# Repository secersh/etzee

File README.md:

# etzee

etzee is an open modular input-device ecosystem. It combines keyboards, utility modules, magnetic pogo-pin connectors, local displays, haptics, and firmware that can discover and communicate across connected modules.

The project is early and hardware-heavy. The current active board is B11; M0 and M9 are planned modules.

## Devices

| Device | Type | Status | Notes |
|--------|------|--------|-------|
| B11 | Primary keyboard board | Active | Split or monoblock keyboard, 5/6 columns per half, switch-family PCB variants |
| M0 | Module | Planned | USB-C module with haptic dial and round touch display |
| M9 | Module | Planned | USB-C 3x3 mechanical keypad with display |

## B11

B11 is the first primary etzee keyboard. Current design goals:

- split or monoblock use
- Bluetooth-first firmware target
- hot-swappable switch carriers
- integrated dot-matrix display on switch plates
- south-facing per-key LEDs
- magnetic pogo-pin module connectors
- 5-column and 6-column half variants
- MX, Choc v2, and KS-33 switch-family variants
- generated KiCad PCB files from tracked MCAD-derived outlines

Current B11 docs:

- [switch compatibility](docs/b11/switch-compatibility.md)
- [switch profiles](docs/b11/switch-profiles.md)
- [keycap compatibility](docs/b11/keycap-compatibility.md)

## Repository Layout

```text
.github/workflows/          GitHub Actions workflows
docs/b11/                   B11 hardware compatibility and profile docs
docs/firmware/              firmware and protocol docs
firmware/                   firmware workspaces
hardware/b11/ecad/          B11 KiCad projects and generated boards
hardware/b11/mcad/          B11 MCAD export config and PCB outlines
hardware/b11/tools/         B11 PCB generation/update tools
hardware/tools/             shared hardware tooling
lib/                        shared KiCad footprints, 3D models, datasheets
```

## Generated PCB Workflow

B11 generated boards are updated through one batch script:

```sh
/Applications/KiCad/KiCad.app/Contents/Frameworks/Python.framework/Versions/Current/bin/python3 hardware/b11/tools/update-pcbs.py --manufacturer jlcpcb --dry-run
```

Remove `--dry-run` to update generated PCB files locally. The updater can generate PCB outlines, place switch sockets, place switch LEDs, place display LEDs, apply manufacturer stackups, and generate manufacturer design rules.

Current generated B11 PCB variants:

| Family | Columns | Boards |
|--------|---------|--------|
| MX | 5, 6 | `LSP`, `RSP`, `LSC`, `RSC` |
| CHOC-V2 | 5, 6 | `LSP`, `RSP`, `LSC`, `RSC` |
| KS-33 | 5, 6 | `LSP`, `RSP`, `LSC`, `RSC` |

Board names use:

```text
ETZ-B11-{board_code}-{columns}-{switch_family}.kicad_pcb
```

Example:

```text
ETZ-B11-LSP-5-KS-33.kicad_pcb
```

## MCAD Exports

B11 MCAD export inputs are defined in [hardware/b11/mcad/parts.yaml](hardware/b11/mcad/parts.yaml). The GitHub workflow exports common parts once and matrix parts once per board variant:

- `5-MX`, `6-MX`
- `5-CHOC-V2`, `6-CHOC-V2`
- `5-KS-33`, `6-KS-33`

PCB outline DXFs live under:

```text
hardware/b11/mcad/pcb-outlines/{MX,CHOC-V2,KS-33}/
```

## Firmware

Firmware is based around ZMK-compatible targets. The htoyto protocol is the project-specific communication concept for inter-module discovery and messaging.

- [htoyto protocol overview](docs/firmware/htoyto.md)

## Contributing

See [CONTRIBUTING.md](CONTRIBUTING.md). The short version: keep generated files reproducible, keep hardware changes scoped, and run the relevant dry-runs before opening a pull request.

For discussion and implementation feedback, join the etzee Discord:

https://discord.gg/y3pcSCghcg

## License

This repository uses different open licenses for different material types. See [LICENSE.md](LICENSE.md) for the full licensing map.

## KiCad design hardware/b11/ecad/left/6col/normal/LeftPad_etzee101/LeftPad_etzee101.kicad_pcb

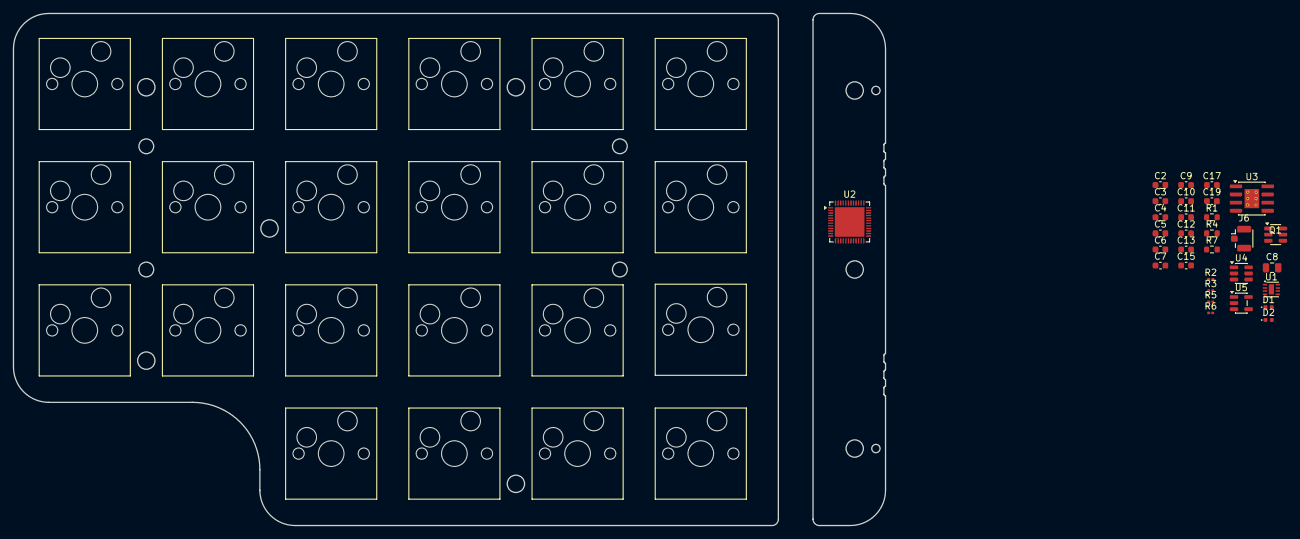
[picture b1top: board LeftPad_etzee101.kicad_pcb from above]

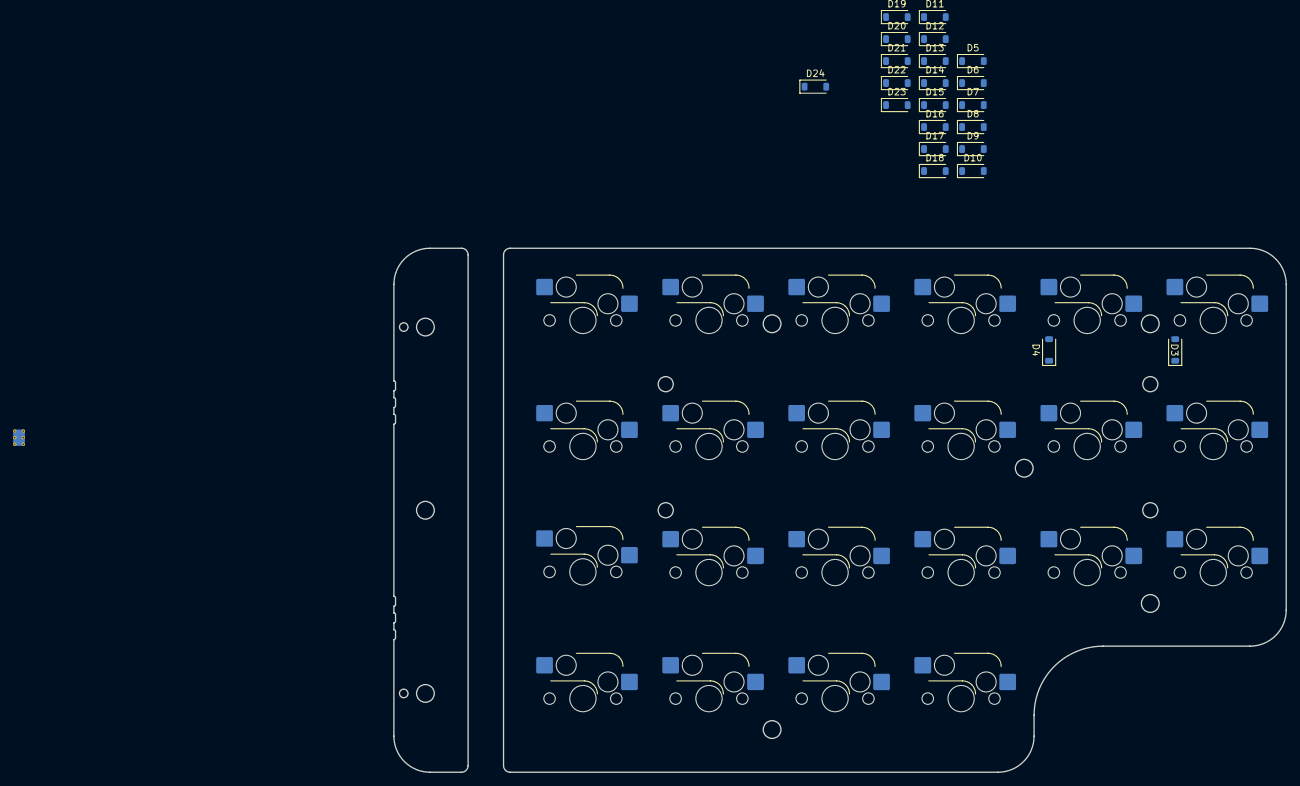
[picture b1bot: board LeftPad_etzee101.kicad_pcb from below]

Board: 4 copper layers, 135.9 x 79.8 mm, 75 parts (22 on the bottom side), 58 nets, no tracks yet.

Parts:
C2: 1uF; C_0603_1608Metric
C3, C4: 100pF; C_0603_1608Metric
C5: 100nF; C_0603_1608Metric
C6, C13, C17, C19: 12pF; C_0603_1608Metric
C7, C12: 100n; C_0603_1608Metric
C8: 10u; C_0805_2012Metric
C9: 1u; C_0603_1608Metric
C10: 10n; C_0603_1608Metric
C11: 10u; C_0603_1608Metric
C15: 1pF; C_0603_1608Metric
D1: RED; D_0402_1005Metric
D2: GRN; D_0402_1005Metric
D3, D4, D5, D6, D7, D8, D9, D10, D11, D12, D13, D14, D15, D16, D17, D18, D19, D20, D21, D22, D23, D24: 1n4148; D_SOD-123
J6: FL; U.FL_Hirose_U.FL-R-SMT-1_Vertical
Q1: FS8205A; FS8205A_SOT23-6
R1: 100; R_0603_1608Metric
R2, R3, R5, R6: 1K2; R_0201_0603Metric
R4, R7: 10K; R_0603_1608Metric
SW1, SW2, SW3, SW4, SW5, SW6, SW7, SW8, SW9, SW10, SW11, SW12, SW13, SW14, SW15, SW16, SW17, SW18, SW19, SW20, SW21, SW22: MX_Switch_Hot_Swappable
U1: MAX17048G; DFN-8-1EP_2x2mm_P0.5mm_EP0.8x1.6mm
U2: nRF52832-QFxx; QFN-48-1EP_6x6mm_P0.4mm_EP4.6x4.6mm
U3: TP4056; SOIC-8-1EP_3.9x4.9mm_P1.27mm_EP2.29x3mm_ThermalVias
U4: DW01; SOT-23-6
U5: XC6220B331MR; SOT-23-5

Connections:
+5V: D1.2 (A), D2.2 (A), U3.4 (VCC), U3.8 (CE)
+VBAT: C8.1, C9.1, C10.1, R1.2, R7.2, U1.2 (CELL), U1.3 (VDD), U3.5 (BAT), U5.1 (VIN)
/ALRT_BAT: R4.2, U1.5 (ALT)
/keyboard_pad_left/COL1: SW1.1, SW7.1, SW13.1
/keyboard_pad_left/COL2: SW2.1, SW8.1, SW14.1
/keyboard_pad_left/COL3: SW3.1, SW9.1, SW15.1, SW19.1
/keyboard_pad_left/COL4: SW4.1, SW10.1, SW16.1, SW20.1
/keyboard_pad_left/COL5: SW5.1, SW11.1, SW17.1, SW21.1
/keyboard_pad_left/COL6: SW6.1, SW12.1, SW18.1, SW22.1
/keyboard_pad_left/ROW1: D3.1 (K), D4.1 (K), D6.1 (K), D7.1 (K), D8.1 (K), D21.1 (K)
/keyboard_pad_left/ROW2: D5.1 (K), D9.1 (K), D10.1 (K), D11.1 (K), D12.1 (K), D22.1 (K)
/keyboard_pad_left/ROW3: D13.1 (K), D14.1 (K), D15.1 (K), D16.1 (K), D17.1 (K), D23.1 (K)
/keyboard_pad_left/ROW4: D18.1 (K), D19.1 (K), D20.1 (K), D24.1 (K)
GND: C2.2, C3.2, C4.2, C5.2, C6.2, C8.2, C9.2, C10.2, C11.2, C12.2, C13.2, C15.2, C17.2, C19.2, J6.2 (Ext), R2.2, U1.1 (CTG), U1.4 (GND), U1.6 (QST), U1.9 (EP), U2.31 (VSS), U2.45 (VSS), U2.49 (VSS), U3.1 (TEMP), U3.3 (GND), U3.9 (EP), U5.2 (GND)
unnamed: D1.1 (K), R3.1
unnamed: D2.1 (K), R5.1
unnamed: D3.2 (A), SW1.2
unnamed: D4.2 (A), SW2.2
unnamed: D5.2 (A), SW7.2
unnamed: D6.2 (A), SW3.2
unnamed: D7.2 (A), SW4.2
unnamed: D8.2 (A), SW5.2
unnamed: D9.2 (A), SW8.2
unnamed: D10.2 (A), SW9.2
unnamed: D11.2 (A), SW10.2
unnamed: D12.2 (A), SW11.2
unnamed: D13.2 (A), SW13.2
unnamed: D14.2 (A), SW14.2
unnamed: D15.2 (A), SW15.2
unnamed: D16.2 (A), SW16.2
unnamed: D17.2 (A), SW17.2
unnamed: D18.2 (A), SW19.2
unnamed: D19.2 (A), SW20.2
unnamed: D20.2 (A), SW21.2
unnamed: D21.2 (A), SW6.2
unnamed: D22.2 (A), SW12.2
unnamed: D23.2 (A), SW18.2
unnamed: D24.2 (A), SW22.2
unnamed: C7.2, Q1.D1/D2, U4.4 (TD)
unnamed: Q1.S1, R6.2
unnamed: C15.1, U2.30 (ANT)
unnamed: C5.1, U2.1 (DEC1)
unnamed: C4.1, U2.32 (DEC2)
unnamed: C3.1, U2.33 (DEC3)
unnamed: C2.1, U2.46 (DEC4)
unnamed: C6.1, U2.2 (P0.00/XL1)
unnamed: C13.1, U2.3 (P0.01/XL2)
unnamed: C17.1, U2.34 (XC1)
unnamed: C19.1, U2.35 (XC2)
unnamed: R3.2, U3.7 (CHRG)
unnamed: R2.1, U3.2 (PROG)
unnamed: R5.2, U3.6 (STDBY)
unnamed: C7.1, R1.1, U4.2 (CS)
unnamed: Q1.G2, U4.3 (OC)
unnamed: Q1.G1, U4.1 (OD)
unnamed: R6.1, U4.5 (VCC)
unnamed: R7.1, U5.3 (CE)
VDD: C11.1, C12.1, R4.1, U2.13 (VDD), U2.36 (VDD), U2.48 (VDD), U5.5 (VOUT)

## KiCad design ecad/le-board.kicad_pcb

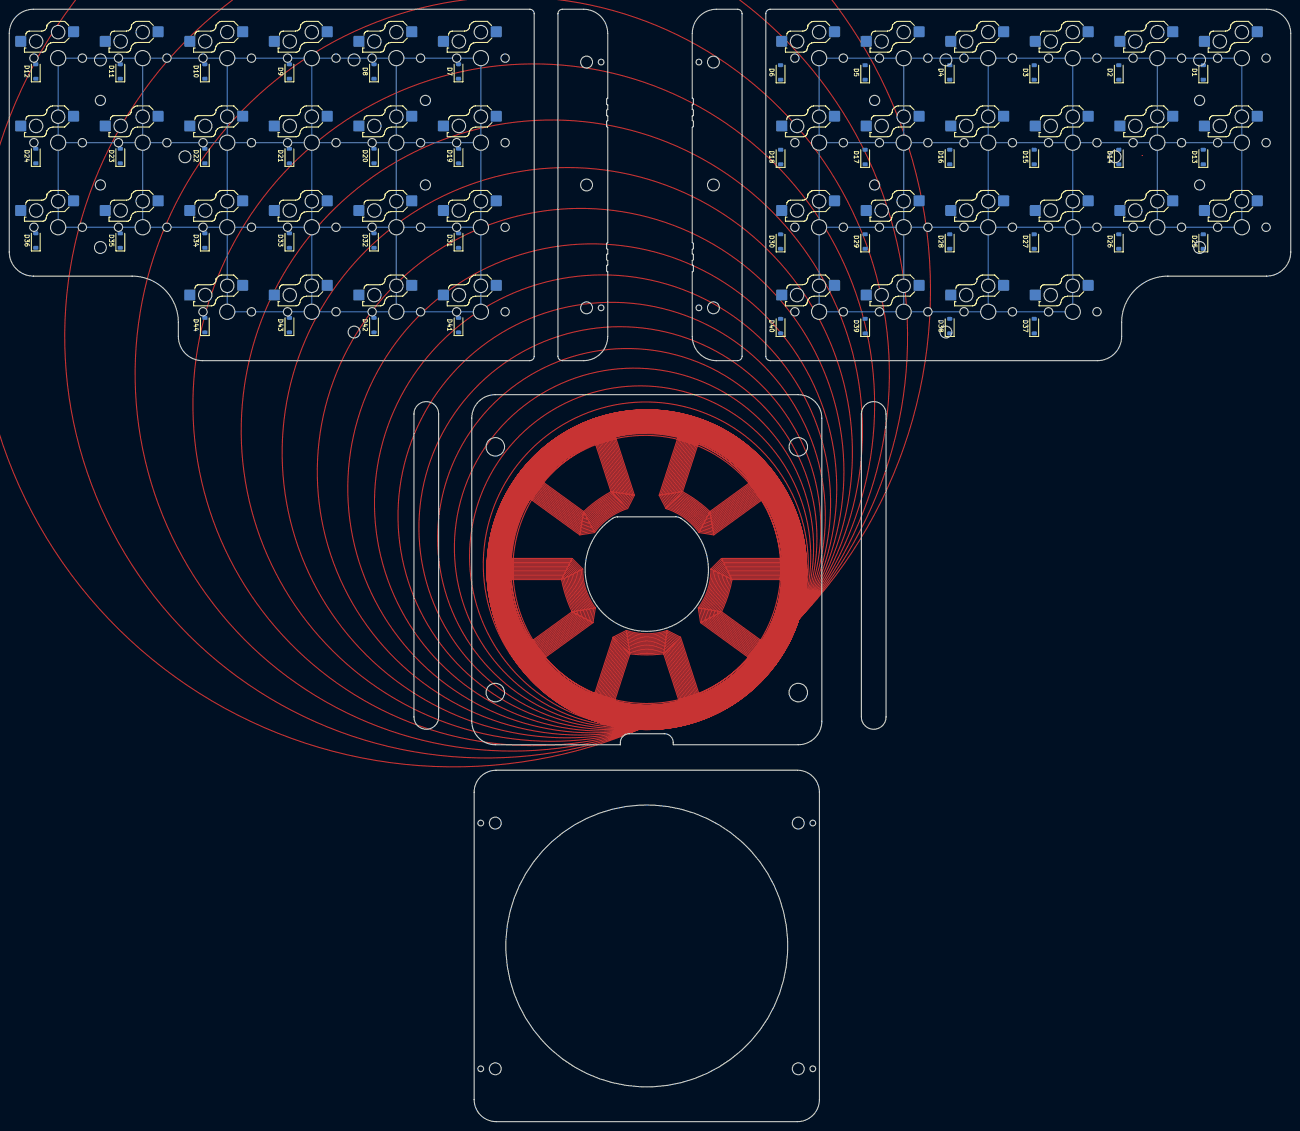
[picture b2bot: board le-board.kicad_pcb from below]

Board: 4 copper layers, 291.0 x 252.6 mm, 88 parts (44 on the bottom side), 44 nets.

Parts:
D1, D2, D3, D4, D5, D6, D7, D8, D9, D10, D11, D12, D13, D14, D15, D16, D17, D18, D19, D20, D21, D22, D23, D24, D25, D26, D27, D28, D29, D30, D31, D32, D33, D34, D35, D36, D37, D38, D39, D40, D41, D42, D43, D44: 1n4148; D_SOD-123
MX1, MX2, MX3, MX4, MX5, MX6, MX7, MX8, MX9, MX10, MX11, MX12, MX13, MX14, MX15, MX16, MX17, MX18, MX19, MX20, MX21, MX22, MX23, MX24, MX25, MX26, MX27, MX28, MX29, MX30, MX31, MX32, MX33, MX34, MX35, MX36, MX37, MX38, MX39, MX40, MX41, MX42, MX43, MX44: SW; SW_Hotswap_Kailh_Choc_V1

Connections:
unnamed: D1.2 (A), MX1.2
unnamed: D2.2 (A), MX2.2
unnamed: D3.2 (A), MX3.2
unnamed: D4.2 (A), MX4.2
unnamed: D5.2 (A), MX5.2
unnamed: D6.2 (A), MX6.2
unnamed: D7.2 (A), MX7.2
unnamed: D8.2 (A), MX8.2
unnamed: D9.2 (A), MX9.2
unnamed: D10.2 (A), MX10.2
unnamed: D11.2 (A), MX11.2
unnamed: D12.2 (A), MX12.2
unnamed: D13.2 (A), MX13.2
unnamed: D14.2 (A), MX14.2
unnamed: D15.2 (A), MX15.2
unnamed: D16.2 (A), MX16.2
unnamed: D17.2 (A), MX17.2
unnamed: D18.2 (A), MX18.2
unnamed: D19.2 (A), MX19.2
unnamed: D20.2 (A), MX20.2
unnamed: D21.2 (A), MX21.2
unnamed: D22.2 (A), MX22.2
unnamed: D23.2 (A), MX23.2
unnamed: D24.2 (A), MX24.2
unnamed: D25.2 (A), MX25.2
unnamed: D26.2 (A), MX26.2
unnamed: D27.2 (A), MX27.2
unnamed: D28.2 (A), MX28.2
unnamed: D29.2 (A), MX29.2
unnamed: D30.2 (A), MX30.2
unnamed: D31.2 (A), MX31.2
unnamed: D32.2 (A), MX32.2
unnamed: D33.2 (A), MX33.2
unnamed: D34.2 (A), MX34.2
unnamed: D35.2 (A), MX35.2
unnamed: D36.2 (A), MX36.2
unnamed: D37.2 (A), MX37.2
unnamed: D38.2 (A), MX38.2
unnamed: D39.2 (A), MX39.2
unnamed: D40.2 (A), MX40.2
unnamed: D41.2 (A), MX41.2
unnamed: D42.2 (A), MX42.2
unnamed: D43.2 (A), MX43.2
unnamed: D44.2 (A), MX44.2

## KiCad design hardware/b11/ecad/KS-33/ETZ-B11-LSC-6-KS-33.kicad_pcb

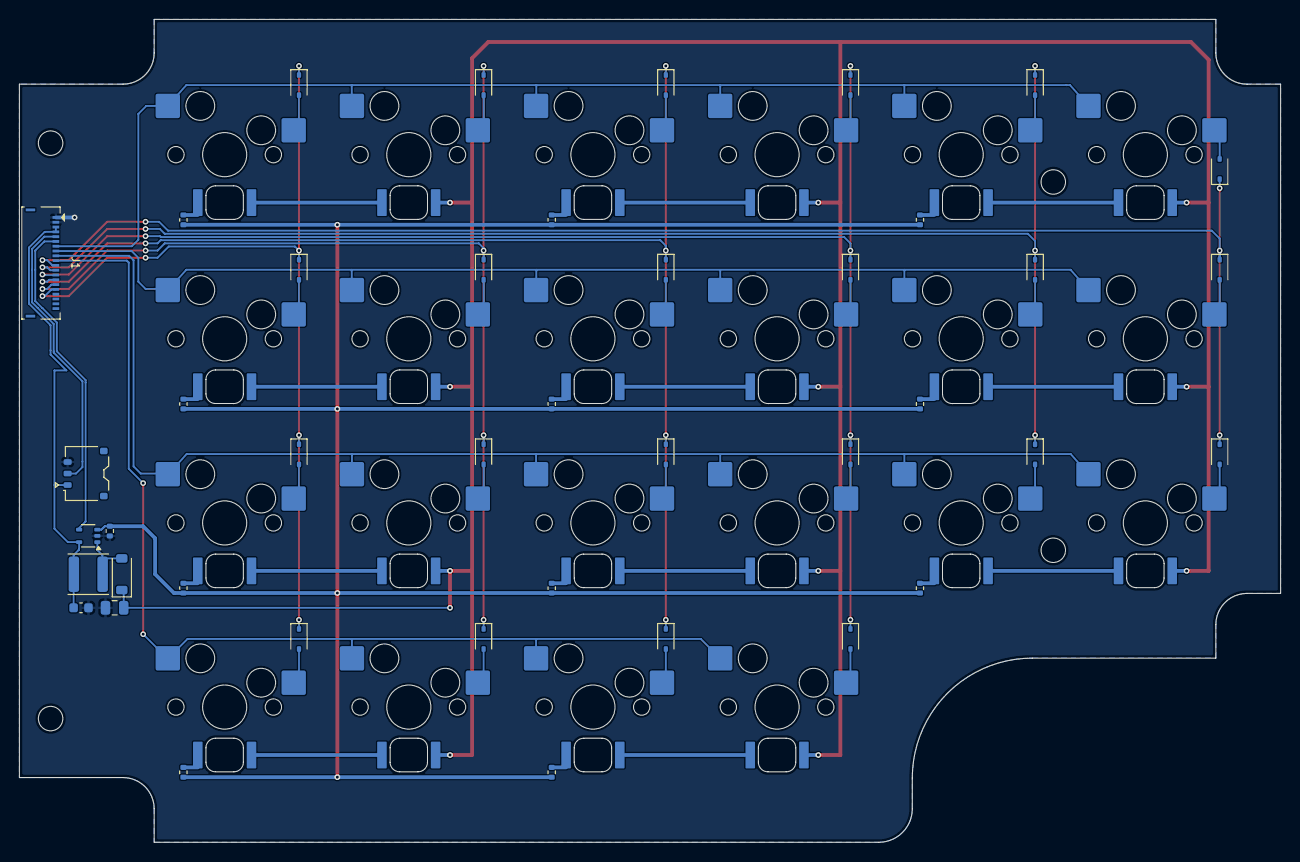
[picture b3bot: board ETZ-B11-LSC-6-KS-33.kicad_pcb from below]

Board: 2 copper layers, 131.5 x 85.8 mm, 85 parts (41 on the bottom side), 61 nets.

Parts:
C1: 4.7uF 10V; C_0603_1608Metric
C2: 1uF 50V; C_0805_2012Metric
D1, D2, D3, D4, D5, D6, D7, D8, D9, D10, D11, D12, D13, D14, D15, D16, D17, D18, D19, D20, D21, D22: 1N4148WS
D23: B5819W; D_SOD-123
J1: 503480-2000
J2: BM03B-ACHSS-GAN-ETF
L1: SWPA4018S100MT; L_Sunlord_SWPA4018S
LED1, LED2, LED3, LED4, LED5, LED6, LED7, LED8, LED9, LED10, LED11, LED12, LED13, LED14, LED15, LED16, LED17, LED18, LED19, LED20, LED21, LED22: 6028_LED
R1: 3.74R 1%; R_0402_1005Metric
R2, R3, R4, R5, R6, R7, R8, R9, R10, R11, R12: 220R 1%; R_0402_1005Metric
SW1, SW2, SW3, SW4, SW5, SW6, SW7, SW8, SW9, SW10, SW11, SW12, SW13, SW14, SW15, SW16, SW17, SW18, SW19, SW20, SW21, SW22: KS-2P02B01-01-a
U1: TPS61169; SOT-353_SC-70-5

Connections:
/BAT_NTC: J1.5, J2.2
/BL_PWM: J1.6, U1.4
/COL0: D1.1, D7.1, D13.1, J1.11
/COL1: D2.1, D8.1, D14.1, J1.12
/COL2: D3.1, D9.1, D15.1, D19.1, J1.13
/COL3: D4.1, D10.1, D16.1, D20.1, J1.14
/COL4: D5.1, D11.1, D17.1, D21.1, J1.15
/COL5: D6.1, D12.1, D18.1, D22.1, J1.16
/ROW0: J1.7, SW1.1, SW2.1, SW3.1, SW4.1, SW5.1, SW6.1
/ROW1: J1.8, SW7.1, SW8.1, SW9.1, SW10.1, SW11.1, SW12.1
/ROW2: J1.9, SW13.1, SW14.1, SW15.1, SW16.1, SW17.1, SW18.1
/ROW3: J1.10, SW19.1, SW20.1, SW21.1, SW22.1
/VBAT: C1.1, J1.3, J1.4, J2.1, L1.1, U1.5
GND: C1.2, C2.2, J1.1, J1.2, J2.3, R1.2, U1.2
unnamed: D23.2, L1.2, U1.1
unnamed: C2.1, D23.1, LED1.2, LED3.2, LED5.2, LED7.2, LED9.2, LED11.2, LED13.2, LED15.2, LED17.2, LED19.2, LED21.2
unnamed: LED1.1, LED2.2
unnamed: LED2.1, R2.1
unnamed: LED3.1, LED4.2
unnamed: LED4.1, R3.1
unnamed: LED5.1, LED6.2
unnamed: LED6.1, R4.1
unnamed: LED7.1, LED8.2
unnamed: LED8.1, R5.1
unnamed: LED9.1, LED10.2
unnamed: LED10.1, R6.1
unnamed: LED11.1, LED12.2
unnamed: LED12.1, R7.1
unnamed: LED13.1, LED14.2
unnamed: LED14.1, R8.1
unnamed: LED15.1, LED16.2
unnamed: LED16.1, R9.1
unnamed: LED17.1, LED18.2
unnamed: LED18.1, R10.1
unnamed: LED19.1, LED20.2
unnamed: LED20.1, R11.1
unnamed: LED21.1, LED22.2
unnamed: LED22.1, R12.1
unnamed: R1.1, R2.2, R3.2, R4.2, R5.2, R6.2, R7.2, R8.2, R9.2, R10.2, R11.2, R12.2, U1.3
SW1: D1.2, SW1.2
SW2: D2.2, SW2.2
SW3: D3.2, SW3.2
SW4: D4.2, SW4.2
SW5: D5.2, SW5.2
SW6: D6.2, SW6.2
SW7: D7.2, SW7.2
SW8: D8.2, SW8.2
SW9: D9.2, SW9.2
SW10: D10.2, SW10.2
SW11: D11.2, SW11.2
SW12: D12.2, SW12.2
SW13: D13.2, SW13.2
SW14: D14.2, SW14.2
SW15: D15.2, SW15.2
SW16: D16.2, SW16.2
SW17: D17.2, SW17.2
SW18: D18.2, SW18.2
SW19: D19.2, SW19.2
SW20: D20.2, SW20.2
SW21: D21.2, SW21.2
SW22: D22.2, SW22.2

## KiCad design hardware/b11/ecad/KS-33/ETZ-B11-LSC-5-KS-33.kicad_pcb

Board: 2 copper layers, 36 parts (0 on the bottom side), 9 nets, no tracks yet.

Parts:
LED1, LED2, LED3, LED4, LED5, LED6, LED7, LED8, LED9, LED10, LED11, LED12, LED13, LED14, LED15, LED16, LED17, LED18: 6028_LED
SW1, SW2, SW3, SW4, SW5, SW6, SW7, SW8, SW9, SW10, SW11, SW12, SW13, SW14, SW15, SW16, SW17, SW18: KS-2P02B01-01-a

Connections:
COL0: SW1.2, SW6.2, SW11.2
COL1: SW2.2, SW7.2, SW12.2
COL2: SW3.2, SW8.2, SW13.2, SW16.2
COL3: SW4.2, SW9.2, SW14.2, SW17.2
COL4: SW5.2, SW10.2, SW15.2, SW18.2
ROW0: SW1.1, SW2.1, SW3.1, SW4.1, SW5.1
ROW1: SW6.1, SW7.1, SW8.1, SW9.1, SW10.1
ROW2: SW11.1, SW12.1, SW13.1, SW14.1, SW15.1
ROW3: SW16.1, SW17.1, SW18.1

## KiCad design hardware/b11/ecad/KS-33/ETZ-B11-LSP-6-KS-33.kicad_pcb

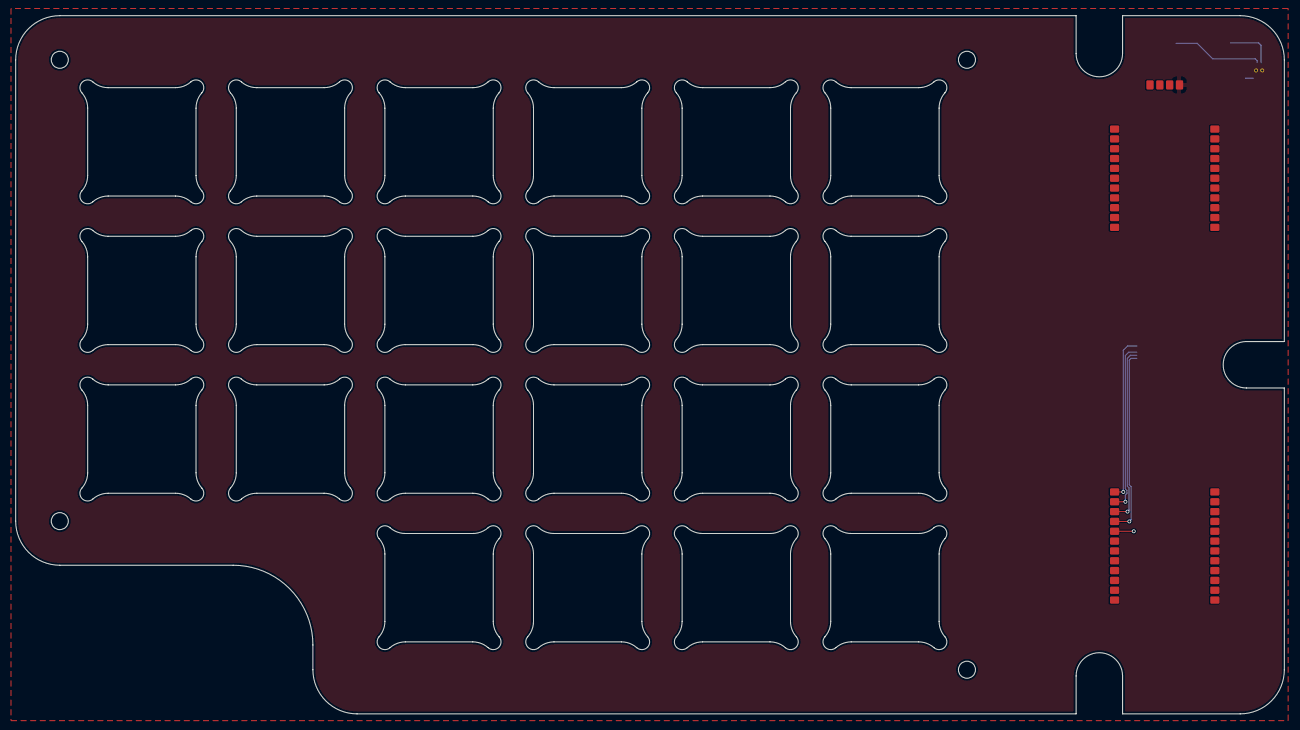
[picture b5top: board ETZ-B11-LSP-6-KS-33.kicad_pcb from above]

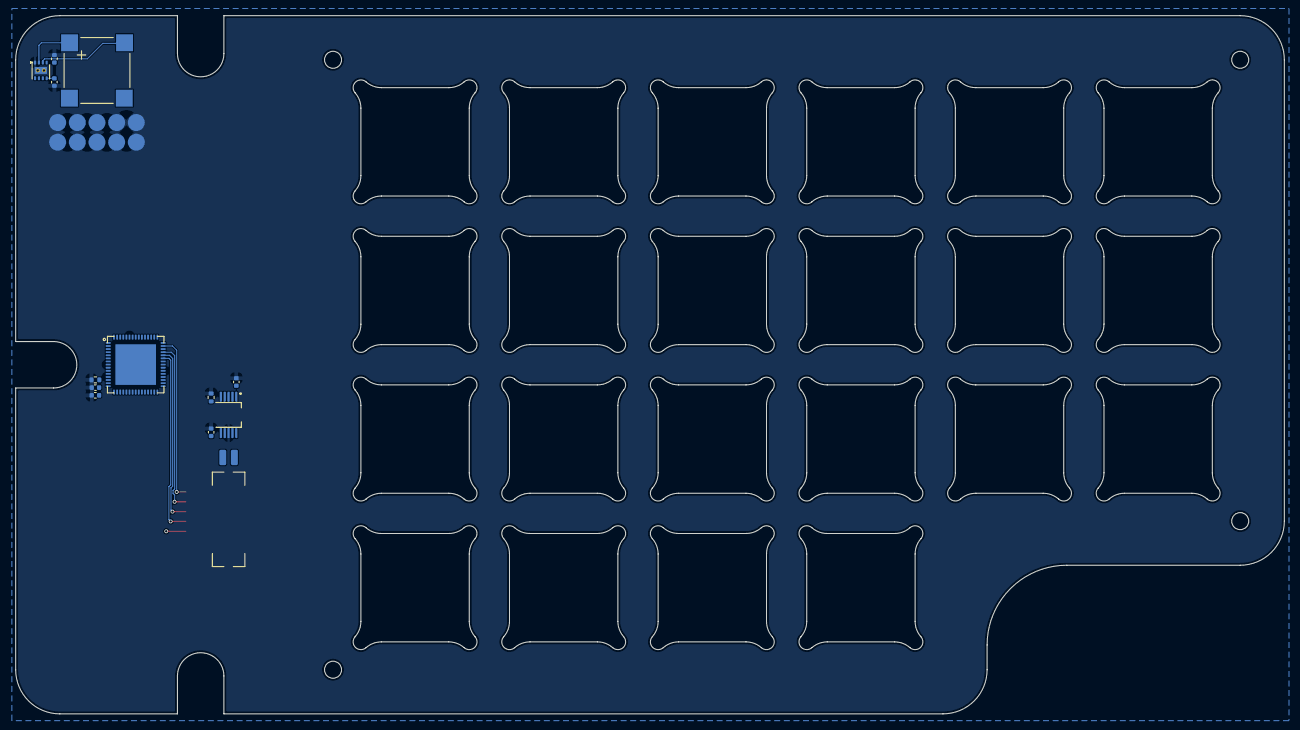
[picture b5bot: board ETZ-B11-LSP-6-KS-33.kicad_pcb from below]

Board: 2 copper layers, 163.9 x 90.2 mm, 15 parts (14 on the bottom side), 61 nets.

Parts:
BZ1: KLJ-8530-3627
C_BUZZ1: 0.1uF
C_BUZZ2: 4.7uF
C_DSP1: 0.1uF
C_DSP2: 4.7uF
C_HAPTIC1: 1uF
C_HAPTIC2: 0.1uF
J_LOGIC1: POGO-PADS-2X5-P2.54
M_LRA1: VLV041235L-L20
R_DSP1: 20k
R_HAPTIC1: 100k
U_BUZZ1: DRV8837DSGR
U_DSP1: IS31FL3741A; IS31FL3741A-QFN-60-7x7
U_DSPMOD1: ETZ-B11-DSP
U_HAPTIC1: DRV2605LDGSR

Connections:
BUZZ_IN1: J_LOGIC1.8, U_BUZZ1.6
BUZZ_IN2: J_LOGIC1.9, U_BUZZ1.5
BUZZ_OUT1: BZ1.1, U_BUZZ1.3
BUZZ_OUT2: BZ1.2, U_BUZZ1.2
DISP_SDB: J_LOGIC1.6, U_DSP1.11
DRV2605_REG: C_HAPTIC1.1, U_HAPTIC1.1
GND: C_BUZZ1.2, C_BUZZ2.2, C_DSP1.2, C_DSP2.2, C_HAPTIC1.2, C_HAPTIC2.2, J_LOGIC1.1, J_LOGIC1.10, R_DSP1.2, R_HAPTIC1.2, U_BUZZ1.4, U_BUZZ1.9, U_DSP1.8, U_DSP1.12, U_DSP1.36, U_DSP1.55, U_DSP1.61, U_DSPMOD1.A4, U_HAPTIC1.8
HAPTIC_EN: J_LOGIC1.7, R_HAPTIC1.1, U_BUZZ1.7, U_HAPTIC1.5
I2C_SCL: J_LOGIC1.4, U_DSP1.10, U_DSPMOD1.A2, U_HAPTIC1.2
I2C_SDA: J_LOGIC1.5, U_DSP1.9, U_DSPMOD1.A3, U_HAPTIC1.3
ISET: R_DSP1.1, U_DSP1.13
LED_CS1: U_DSP1.26, U_DSPMOD1.28
LED_CS2: U_DSP1.27, U_DSPMOD1.27
LED_CS3: U_DSP1.28, U_DSPMOD1.26
LED_CS4: U_DSP1.29, U_DSPMOD1.25
LED_CS5: U_DSP1.30, U_DSPMOD1.24
LED_CS6: U_DSP1.31, U_DSPMOD1.23
LED_CS7: U_DSP1.32, U_DSPMOD1.22
LED_CS8: U_DSP1.33, U_DSPMOD1.21
LED_CS9: U_DSP1.34, U_DSPMOD1.20
LED_CS10: U_DSP1.35, U_DSPMOD1.19
LED_CS11: U_DSP1.37, U_DSPMOD1.18
LED_CS12: U_DSP1.38, U_DSPMOD1.17
LED_CS13: U_DSP1.39, U_DSPMOD1.16
LED_CS14: U_DSP1.40, U_DSPMOD1.15
LED_CS15: U_DSP1.41, U_DSPMOD1.14
LED_CS16: U_DSP1.42, U_DSPMOD1.13
LED_CS17: U_DSP1.43, U_DSPMOD1.36
LED_CS18: U_DSP1.44, U_DSPMOD1.12
LED_CS19: U_DSP1.45, U_DSPMOD1.11
LED_CS20: U_DSP1.46, U_DSPMOD1.10
LED_CS21: U_DSP1.47, U_DSPMOD1.9
LED_CS22: U_DSP1.48, U_DSPMOD1.8
LED_CS23: U_DSP1.49, U_DSPMOD1.7
LED_CS24: U_DSP1.50, U_DSPMOD1.6
LED_CS25: U_DSP1.51, U_DSPMOD1.5
LED_CS26: U_DSP1.52, U_DSPMOD1.4
LED_CS27: U_DSP1.53, U_DSPMOD1.3
LED_CS28: U_DSP1.54, U_DSPMOD1.2
LED_CS29: U_DSP1.56, U_DSPMOD1.1
LED_CS30: U_DSP1.57, U_DSPMOD1.46
LED_CS31: U_DSP1.58, U_DSPMOD1.45
LED_CS32: U_DSP1.59, U_DSPMOD1.44
LED_CS33: U_DSP1.60, U_DSPMOD1.43
LED_CS34: U_DSP1.1, U_DSPMOD1.42
LED_CS35: U_DSP1.2, U_DSPMOD1.41
LED_CS36: U_DSP1.3, U_DSPMOD1.40
LED_CS37: U_DSP1.4, U_DSPMOD1.39
LED_CS38: U_DSP1.5, U_DSPMOD1.38
LED_CS39: U_DSP1.6, U_DSPMOD1.37
LED_SW1: U_DSP1.16, U_DSPMOD1.35
LED_SW2: U_DSP1.17, U_DSPMOD1.34
LED_SW3: U_DSP1.18, U_DSPMOD1.33
LED_SW4: U_DSP1.19, U_DSPMOD1.32
LED_SW5: U_DSP1.20, U_DSPMOD1.31
LED_SW6: U_DSP1.21, U_DSPMOD1.30
LED_SW7: U_DSP1.22, U_DSPMOD1.29
LRA_OUTN: M_LRA1.2, U_HAPTIC1.9
LRA_OUTP: M_LRA1.1, U_HAPTIC1.7
SP_VDD: C_BUZZ1.1, C_BUZZ2.1, C_DSP1.1, C_DSP2.1, C_HAPTIC2.1, J_LOGIC1.3, U_BUZZ1.8, U_DSP1.14, U_DSP1.15, U_DSP1.25, U_DSPMOD1.A1
VBAT: J_LOGIC1.2, U_BUZZ1.1, U_HAPTIC1.6, U_HAPTIC1.10

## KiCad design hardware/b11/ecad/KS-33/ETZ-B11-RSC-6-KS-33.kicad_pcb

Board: 2 copper layers, 44 parts (0 on the bottom side), 10 nets, no tracks yet.

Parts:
LED1, LED2, LED3, LED4, LED5, LED6, LED7, LED8, LED9, LED10, LED11, LED12, LED13, LED14, LED15, LED16, LED17, LED18, LED19, LED20, LED21, LED22: 6028_LED
SW1, SW2, SW3, SW4, SW5, SW6, SW7, SW8, SW9, SW10, SW11, SW12, SW13, SW14, SW15, SW16, SW17, SW18, SW19, SW20, SW21, SW22: KS-2P02B01-01-a

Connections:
COL0: SW1.2, SW7.2, SW13.2
COL1: SW2.2, SW8.2, SW14.2
COL2: SW3.2, SW9.2, SW15.2, SW19.2
COL3: SW4.2, SW10.2, SW16.2, SW20.2
COL4: SW5.2, SW11.2, SW17.2, SW21.2
COL5: SW6.2, SW12.2, SW18.2, SW22.2
ROW0: SW1.1, SW2.1, SW3.1, SW4.1, SW5.1, SW6.1
ROW1: SW7.1, SW8.1, SW9.1, SW10.1, SW11.1, SW12.1
ROW2: SW13.1, SW14.1, SW15.1, SW16.1, SW17.1, SW18.1
ROW3: SW19.1, SW20.1, SW21.1, SW22.1

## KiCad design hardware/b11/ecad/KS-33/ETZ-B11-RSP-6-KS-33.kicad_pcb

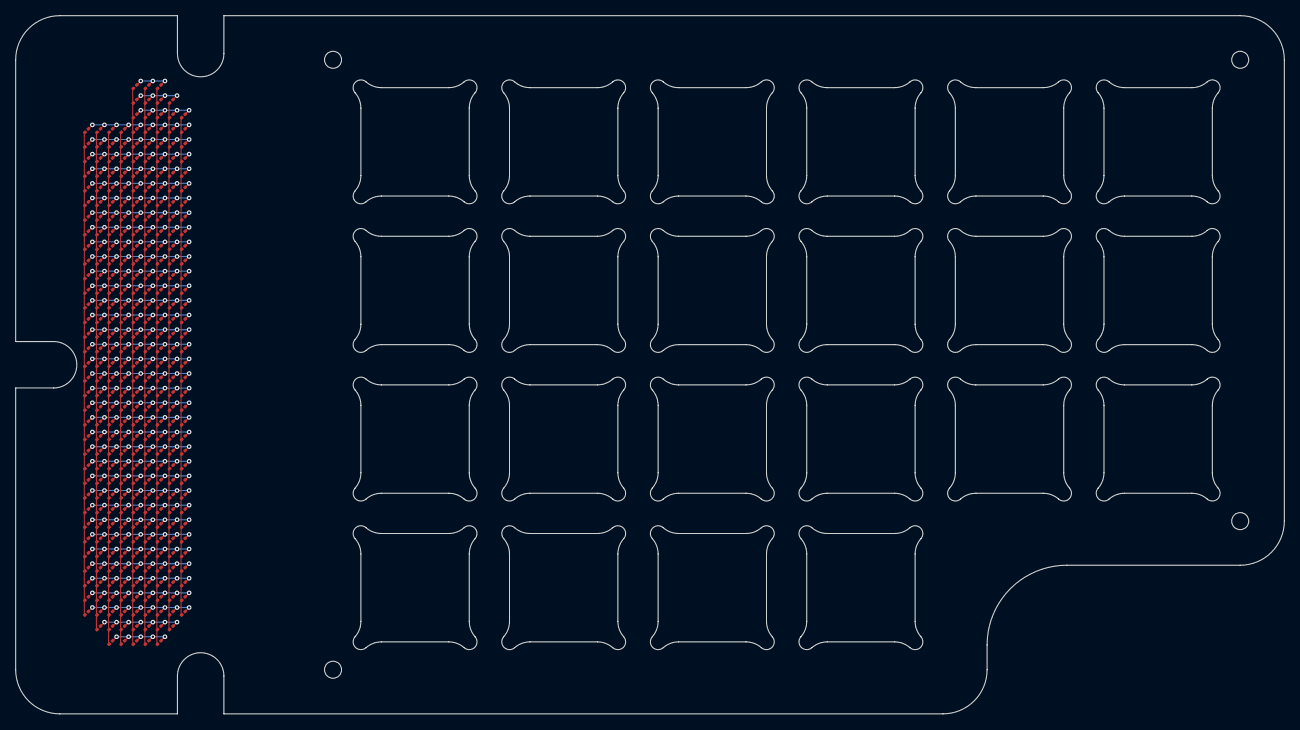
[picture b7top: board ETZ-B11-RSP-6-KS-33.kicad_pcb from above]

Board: 2 copper layers, 163.9 x 90.2 mm, 330 parts (0 on the bottom side), 48 nets.

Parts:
D1, D2, D3, D4, D5, D6, D7, D8, D9, D10, D11, D12, D13, D14, D15, D16, D17, D18, D19, D20, D21, D22, D23, D24, D25, D26, D27, D28, D29, D30, D31, D32, D33, D34, D35, D36, D37, D38, D39, D40, D41, D42, D43, D44, D45, D46, D47, D48, D49, D50, D51, D52, D53, D54, D55, D56, D57, D58, D59, D60, D61, D62, D63, D64, D65, D66, D67, D68, D69, D70, D71, D72, D73, D74, D75, D76, D77, D78, D79, D80, D81, D82, D83, D84, D85, D86, D87, D88, D89, D90, D91, D92, D93, D94, D95, D96, D97, D98, D99, D100, D101, D102, D103, D104, D105, D106, D107, D108, D109, D110, D111, D112, D113, D114, D115, D116, D117, D118, D119, D120, D121, D122, D123, D124, D125, D126, D127, D128, D129, D130, D131, D132, D133, D134, D135, D136, D137, D138, D139, D140, D141, D142, D143, D144, D145, D146, D147, D148, D149, D150, D151, D152, D153, D154, D155, D156, D157, D158, D159, D160, D161, D162, D163, D164, D165, D166, D167, D168, D169, D170, D171, D172, D173, D174, D175, D176, D177, D178, D179, D180, D181, D182, D183, D184, D185, D186, D187, D188, D189, D190, D191, D192, D193, D194, D195, D196, D197, D198, D199, D200, D201, D202, D203, D204, D205, D206, D207, D208, D209, D210, D211, D212, D213, D214, D215, D216, D217, D218, D219, D220, D221, D222, D223, D224, D225, D226, D227, D228, D229, D230, D231, D232, D233, D234, D235, D236, D237, D238, D239, D240, D241, D242, D243, D244, D245, D246, D247, D248, D249, D250, D251, D252, D253, D254, D255, D256, D257, D258, D259, D260, D261, D262, D263, D264, D265, D266, D267, D268, D269, D270, D271, D272, D273, D274, D275, D276, D277, D278, D279, D280, D281, D282, D283, D284, D285, D286, D287, D288, D289, D290, D291, D292, D293, D294, D295, D296, D297, D298, D299, D300, D301, D302, D303, D304, D305, D306, D307, D308, D309, D310, D311, D312, D313, D314, D315, D316, D317, D318, D319, D320, D321, D322, D323, D324, D325, D326, D327, D328, D329, D330: 0201_LED

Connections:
LED_CS1: D1.1, D2.1, D3.1
LED_CS2: D4.1, D5.1, D6.1, D7.1
LED_CS3: D8.1, D9.1, D10.1, D11.1, D12.1
LED_CS4: D13.1, D14.1, D15.1, D16.1, D17.1, D18.1, D19.1, D20.1, D21.1
LED_CS5: D22.1, D23.1, D24.1, D25.1, D26.1, D27.1, D28.1, D29.1, D30.1
LED_CS6: D31.1, D32.1, D33.1, D34.1, D35.1, D36.1, D37.1, D38.1, D39.1
LED_CS7: D40.1, D41.1, D42.1, D43.1, D44.1, D45.1, D46.1, D47.1, D48.1
LED_CS8: D49.1, D50.1, D51.1, D52.1, D53.1, D54.1, D55.1, D56.1, D57.1
LED_CS9: D58.1, D59.1, D60.1, D61.1, D62.1, D63.1, D64.1, D65.1, D66.1
LED_CS10: D67.1, D68.1, D69.1, D70.1, D71.1, D72.1, D73.1, D74.1, D75.1
LED_CS11: D76.1, D77.1, D78.1, D79.1, D80.1, D81.1, D82.1, D83.1, D84.1
LED_CS12: D85.1, D86.1, D87.1, D88.1, D89.1, D90.1, D91.1, D92.1, D93.1
LED_CS13: D94.1, D95.1, D96.1, D97.1, D98.1, D99.1, D100.1, D101.1, D102.1
LED_CS14: D103.1, D104.1, D105.1, D106.1, D107.1, D108.1, D109.1, D110.1, D111.1
LED_CS15: D112.1, D113.1, D114.1, D115.1, D116.1, D117.1, D118.1, D119.1, D120.1
LED_CS16: D121.1, D122.1, D123.1, D124.1, D125.1, D126.1, D127.1, D128.1, D129.1
LED_CS17: D130.1, D131.1, D132.1, D133.1, D134.1, D135.1, D136.1, D137.1, D138.1
LED_CS18: D139.1, D140.1, D141.1, D142.1, D143.1, D144.1, D145.1, D146.1, D147.1
LED_CS19: D148.1, D149.1, D150.1, D151.1, D152.1, D153.1, D154.1, D155.1, D156.1
LED_CS20: D157.1, D158.1, D159.1, D160.1, D161.1, D162.1, D163.1, D164.1, D165.1
LED_CS21: D166.1, D167.1, D168.1, D169.1, D170.1, D171.1, D172.1, D173.1, D174.1
LED_CS22: D175.1, D176.1, D177.1, D178.1, D179.1, D180.1, D181.1, D182.1, D183.1
LED_CS23: D184.1, D185.1, D186.1, D187.1, D188.1, D189.1, D190.1, D191.1, D192.1
LED_CS24: D193.1, D194.1, D195.1, D196.1, D197.1, D198.1, D199.1, D200.1, D201.1
LED_CS25: D202.1, D203.1, D204.1, D205.1, D206.1, D207.1, D208.1, D209.1, D210.1
LED_CS26: D211.1, D212.1, D213.1, D214.1, D215.1, D216.1, D217.1, D218.1, D219.1
LED_CS27: D220.1, D221.1, D222.1, D223.1, D224.1, D225.1, D226.1, D227.1, D228.1
LED_CS28: D229.1, D230.1, D231.1, D232.1, D233.1, D234.1, D235.1, D236.1, D237.1
LED_CS29: D238.1, D239.1, D240.1, D241.1, D242.1, D243.1, D244.1, D245.1, D246.1
LED_CS30: D247.1, D248.1, D249.1, D250.1, D251.1, D252.1, D253.1, D254.1, D255.1
LED_CS31: D256.1, D257.1, D258.1, D259.1, D260.1, D261.1, D262.1, D263.1, D264.1
LED_CS32: D265.1, D266.1, D267.1, D268.1, D269.1, D270.1, D271.1, D272.1, D273.1
LED_CS33: D274.1, D275.1, D276.1, D277.1, D278.1, D279.1, D280.1, D281.1, D282.1
LED_CS34: D283.1, D284.1, D285.1, D286.1, D287.1, D288.1, D289.1, D290.1, D291.1
LED_CS35: D292.1, D293.1, D294.1, D295.1, D296.1, D297.1, D298.1, D299.1, D300.1
LED_CS36: D301.1, D302.1, D303.1, D304.1, D305.1, D306.1, D307.1, D308.1, D309.1
LED_CS37: D310.1, D311.1, D312.1, D313.1, D314.1, D315.1, D316.1, D317.1, D318.1
LED_CS38: D319.1, D320.1, D321.1, D322.1, D323.1, D324.1, D325.1
LED_CS39: D326.1, D327.1, D328.1, D329.1, D330.1
LED_SW1: D13.2, D22.2, D31.2, D40.2, D49.2, D58.2, D67.2, D76.2, D85.2, D94.2, D103.2, D112.2, D121.2, D130.2, D139.2, D148.2, D157.2, D166.2, D175.2, D184.2, D193.2, D202.2, D211.2, D220.2, D229.2, D238.2, D247.2, D256.2, D265.2, D274.2, D283.2, D292.2, D301.2, D310.2
LED_SW2: D14.2, D23.2, D32.2, D41.2, D50.2, D59.2, D68.2, D77.2, D86.2, D95.2, D104.2, D113.2, D122.2, D131.2, D140.2, D149.2, D158.2, D167.2, D176.2, D185.2, D194.2, D203.2, D212.2, D221.2, D230.2, D239.2, D248.2, D257.2, D266.2, D275.2, D284.2, D293.2, D302.2, D311.2, D319.2
LED_SW3: D15.2, D24.2, D33.2, D42.2, D51.2, D60.2, D69.2, D78.2, D87.2, D96.2, D105.2, D114.2, D123.2, D132.2, D141.2, D150.2, D159.2, D168.2, D177.2, D186.2, D195.2, D204.2, D213.2, D222.2, D231.2, D240.2, D249.2, D258.2, D267.2, D276.2, D285.2, D294.2, D303.2, D312.2, D320.2, D326.2
LED_SW4: D16.2, D25.2, D34.2, D43.2, D52.2, D61.2, D70.2, D79.2, D88.2, D97.2, D106.2, D115.2, D124.2, D133.2, D142.2, D151.2, D160.2, D169.2, D178.2, D187.2, D196.2, D205.2, D214.2, D223.2, D232.2, D241.2, D250.2, D259.2, D268.2, D277.2, D286.2, D295.2, D304.2, D313.2, D321.2, D327.2
LED_SW5: D1.2, D4.2, D8.2, D17.2, D26.2, D35.2, D44.2, D53.2, D62.2, D71.2, D80.2, D89.2, D98.2, D107.2, D116.2, D125.2, D134.2, D143.2, D152.2, D161.2, D170.2, D179.2, D188.2, D197.2, D206.2, D215.2, D224.2, D233.2, D242.2, D251.2, D260.2, D269.2, D278.2, D287.2, D296.2, D305.2, D314.2, D322.2, D328.2
LED_SW6: D2.2, D5.2, D9.2, D18.2, D27.2, D36.2, D45.2, D54.2, D63.2, D72.2, D81.2, D90.2, D99.2, D108.2, D117.2, D126.2, D135.2, D144.2, D153.2, D162.2, D171.2, D180.2, D189.2, D198.2, D207.2, D216.2, D225.2, D234.2, D243.2, D252.2, D261.2, D270.2, D279.2, D288.2, D297.2, D306.2, D315.2, D323.2, D329.2
LED_SW7: D3.2, D6.2, D10.2, D19.2, D28.2, D37.2, D46.2, D55.2, D64.2, D73.2, D82.2, D91.2, D100.2, D109.2, D118.2, D127.2, D136.2, D145.2, D154.2, D163.2, D172.2, D181.2, D190.2, D199.2, D208.2, D217.2, D226.2, D235.2, D244.2, D253.2, D262.2, D271.2, D280.2, D289.2, D298.2, D307.2, D316.2, D324.2, D330.2
LED_SW8: D7.2, D11.2, D20.2, D29.2, D38.2, D47.2, D56.2, D65.2, D74.2, D83.2, D92.2, D101.2, D110.2, D119.2, D128.2, D137.2, D146.2, D155.2, D164.2, D173.2, D182.2, D191.2, D200.2, D209.2, D218.2, D227.2, D236.2, D245.2, D254.2, D263.2, D272.2, D281.2, D290.2, D299.2, D308.2, D317.2, D325.2
LED_SW9: D12.2, D21.2, D30.2, D39.2, D48.2, D57.2, D66.2, D75.2, D84.2, D93.2, D102.2, D111.2, D120.2, D129.2, D138.2, D147.2, D156.2, D165.2, D174.2, D183.2, D192.2, D201.2, D210.2, D219.2, D228.2, D237.2, D246.2, D255.2, D264.2, D273.2, D282.2, D291.2, D300.2, D309.2, D318.2
